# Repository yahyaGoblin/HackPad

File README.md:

# HACKPAD
A compact 4-key macropad powered by the Seeed XIAO, with a rotary encoder for volume, scroll, or whatever feels useful that week. Fully custom PCB, hand-routed, with MX-compatible switch footprints at 19.05mm spacing.
This was the project that started everything — a Hack Club Hackpad build that turned into a crash course in KiCad, footprint libraries, PCB layout, and knowing when to scale back (and when not to). It taught the fundamentals that every later project relied on.

### Schematic Preview

### PCB Preview

### 3D Model

## Features
- 4 mechanical key switches
- 1 rotary encoder (clicky, EC11)
- Seeed XIAO MCU (small footprint, USB-C)
- Compact single PCB design

### Bill of Materials
| Component | Part | Quantity | Notes | Link | Distributor |
|---|---|---|---|---|---|
| Microcontroller | Seeed XIAO RP2040 | 1 | | [Link](https://keebd.com/products/xiao-rp2040-controller?_pos=1&_psq=xiao&_ss=e&_v=1.0) | KEEBD |
| Switches | MX-compatible mechanical switches (Gateron Blue) | 4 | 5-pin or 3-pin | [Link](https://keebd.com/products/gateron-blue) | KEEBD |
| Keycaps | MX keycaps | 4 | | — | local |
| Rotary Encoder | EC11 rotary encoder | 1 | With push switch | [Link](https://keebd.com/products/ec11-encoder-with-switch?_pos=1&_psq=enco&_ss=e&_v=1.0) | KEEBD |
| Encoder Knob | 3D Printed EC11-compatible knob | 1 | | [Link](https://keebd.com/products/3d-printed-encoder-knob?variant=40383061917848) | KEEBD |
| PCB | Custom (this repo) | 1 | Gerbers in `/gerbers` | — | PCBWay |
| Baseplate | Laser cut / 3D printed | 1 | Holds the PCB | — | local |
| USB Cable | USB-C | 1 | | — | local |

---

## Fabrication
Gerber files are in the `/gerbers` folder, ready to send to JLCPCB, PCBWay, or your preferred fab.

## Firmware
Designed for use with [KMK](https://github.com/KMKfw/kmk_firmware). See `code.py` for the full config — 4 keys mapped to media controls, encoder for volume with mute on press.

## License
Open source hardware — feel free to modify and build your own.

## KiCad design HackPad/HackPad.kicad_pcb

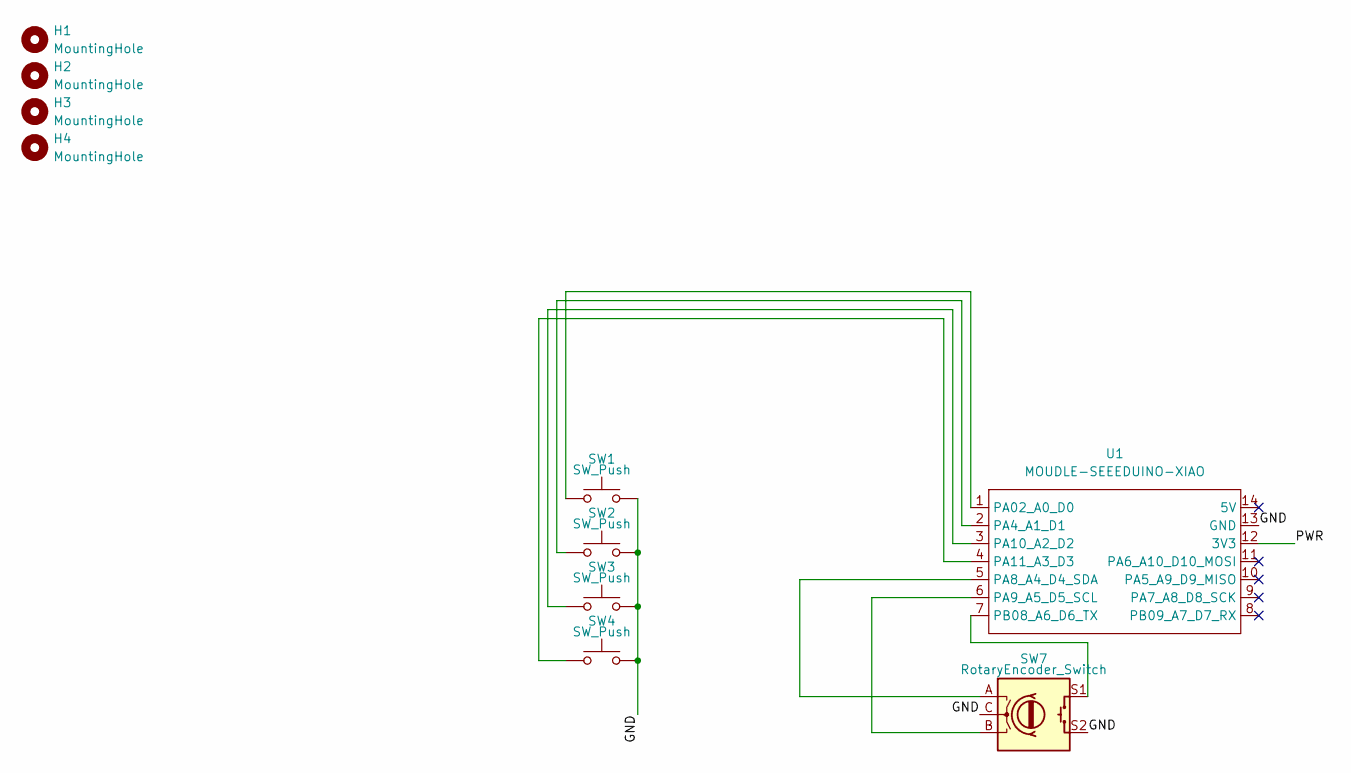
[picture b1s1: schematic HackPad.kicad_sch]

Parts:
H1, H2, H3, H4: MountingHole; MountingHole_3.2mm_M3
SW1, SW2, SW3, SW4: SW_Push; SW_Cherry_MX_1.00u_PCB
SW7: RotaryEncoder_Switch; RotaryEncoder_Alps_EC11E-Switch_Vertical_H20mm
U1: MOUDLE-SEEEDUINO-XIAO; XIAO-Generic-Hybrid-14P-2.54-21X17.8MM

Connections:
/GND: SW1.2, SW2.2, SW3.2, SW4.2, SW7.C, SW7.S2, U1.13 (GND)
/PWR: U1.12 (3V3)
unnamed: SW1.1, U1.1 (PA02_A0_D0)
unnamed: SW2.1, U1.2 (PA4_A1_D1)
unnamed: SW7.A, U1.5 (PA8_A4_D4_SDA)
unnamed: SW7.B, U1.6 (PA9_A5_D5_SCL)
unnamed: SW3.1, U1.3 (PA10_A2_D2)
unnamed: SW4.1, U1.4 (PA11_A3_D3)
unnamed: SW7.S1, U1.7 (PB08_A6_D6_TX)

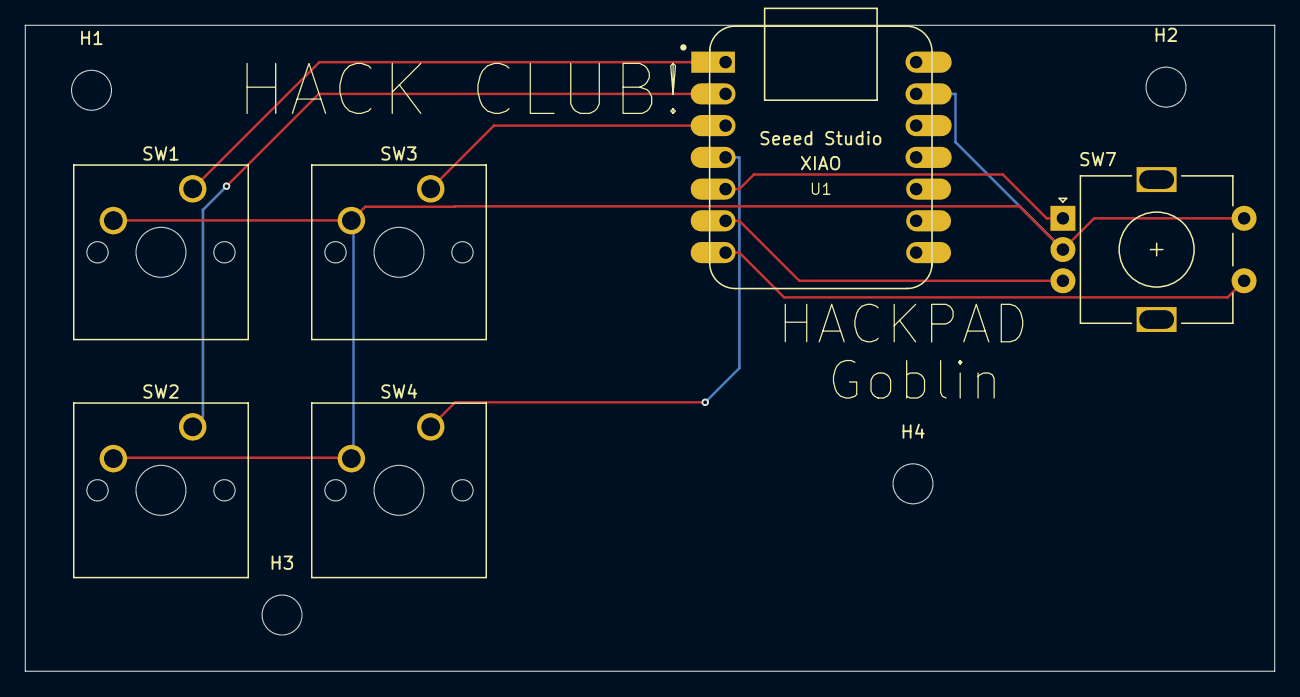
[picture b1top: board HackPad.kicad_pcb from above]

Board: 2 copper layers, 100.0 x 51.7 mm, 10 parts (0 on the bottom side), 8 nets.

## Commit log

2026-05-26 Revise README with updated project details
    Updated project description, features, and bill of materials to reflect changes in components and design.
2026-05-26 Revise image formatting for schematic and PCB previews
    Updated image sections for schematic and PCB previews in README.
2026-05-26 Fix formatting of section headers in README.md
2026-05-29 gerber
2026-06-08 Clarify firmware compatibility in README
    Removed reference to QMK firmware from the README.
2026-06-08 Revise README for 4-key macropad specifications
    Updated the project description, features, and bill of materials to reflect changes in the macropad design and components.
2026-06-08 Update README with fabrication and firmware information
    Added sections for fabrication and firmware details.
2026-06-08 final build with updated code and schematics
2026-06-08 updated gerbers
2026-06-08 step file
2026-06-08 final assembly
2026-06-10 Add Bill of Materials to README
    Added Bill of Materials section with detailed components and links.
2026-06-10 Update README with project details and images
    Added additional images and details about the project features, fabrication, and firmware.
2026-06-10 BOM upload
